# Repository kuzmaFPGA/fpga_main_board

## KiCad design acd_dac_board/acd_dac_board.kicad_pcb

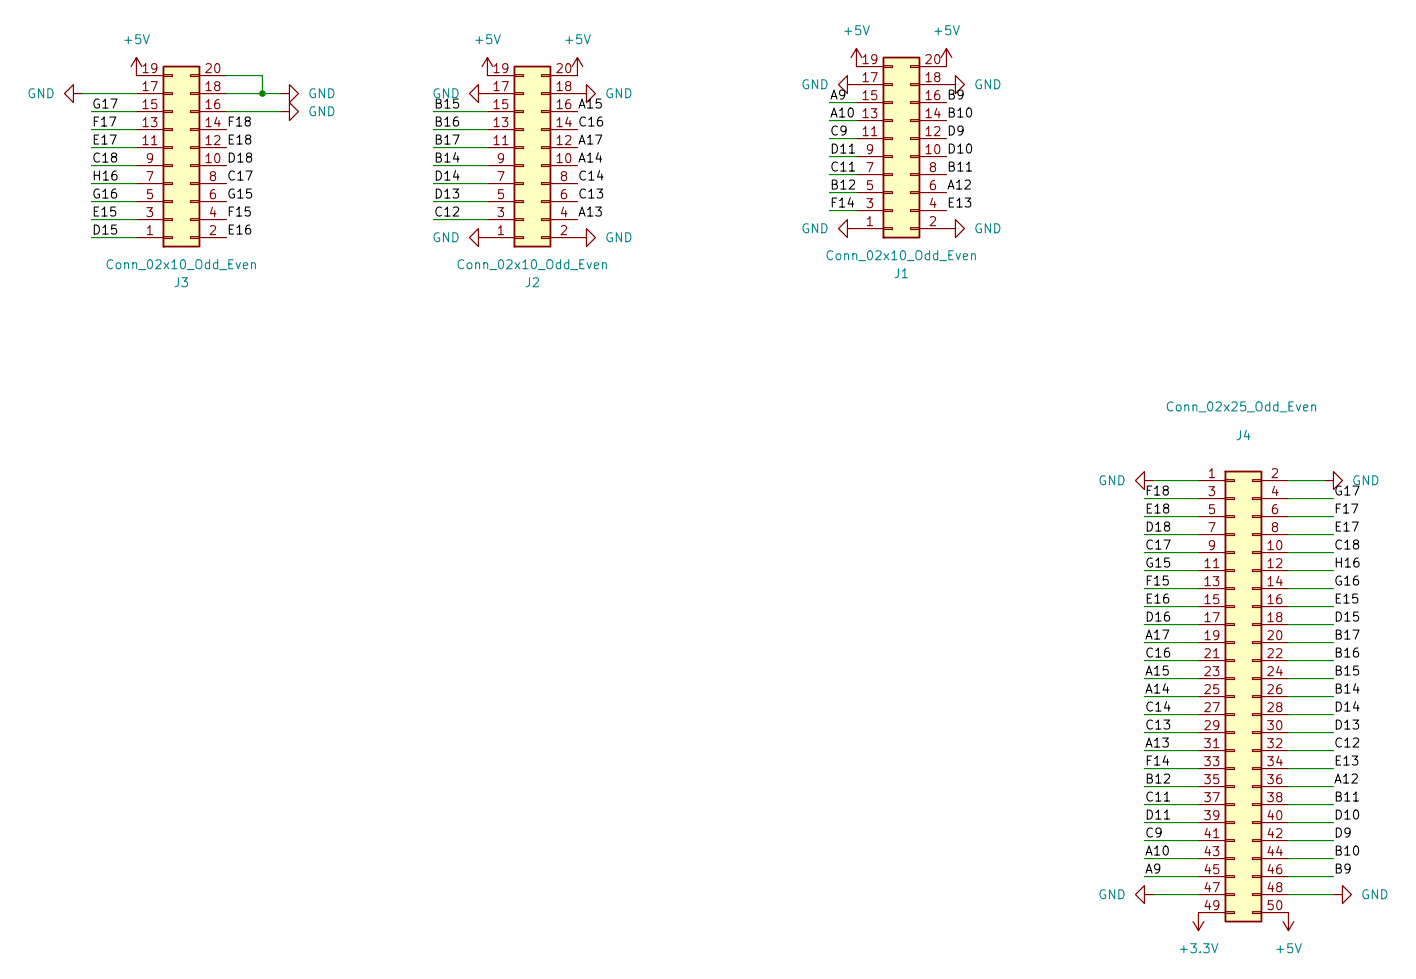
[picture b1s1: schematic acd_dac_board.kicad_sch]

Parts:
J1, J2, J3: Conn_02x10_Odd_Even; PinSocket_2x10_P2.54mm_Vertical
J4: Conn_02x25_Odd_Even; PinHeader_2x25_P2.54mm_Horizontal

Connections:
+3.3V: J4.49
+5V: J1.19, J1.20, J2.19, J2.20, J3.19, J4.50
/A9: J1.15, J4.45
/A10: J1.13, J4.43
/A12: J1.6, J4.36
/A13: J2.4, J4.31
/A14: J2.10, J4.25
/A15: J2.16, J4.23
/A17: J2.12, J4.19
/B9: J1.16, J4.46
/B10: J1.14, J4.44
/B11: J1.8, J4.38
/B12: J1.5, J4.35
/B14: J2.9, J4.26
/B15: J2.15, J4.24
/B16: J2.13, J4.22
/B17: J2.11, J4.20
/C9: J1.11, J4.41
/C11: J1.7, J4.37
/C12: J2.3, J4.32
/C13: J2.6, J4.29
/C14: J2.8, J4.27
/C16: J2.14, J4.21
/C17: J3.8, J4.9
/C18: J3.9, J4.10
/D9: J1.12, J4.42
/D10: J1.10, J4.40
/D11: J1.9, J4.39
/D13: J2.5, J4.30
/D14: J2.7, J4.28
/D15: J3.1, J4.18
/D16: J4.17
/D18: J3.10, J4.7
/E13: J1.4, J4.34
/E15: J3.3, J4.16
/E16: J3.2, J4.15
/E17: J3.11, J4.8
/E18: J3.12, J4.5
/F14: J1.3, J4.33
/F15: J3.4, J4.13
/F17: J3.13, J4.6
/F18: J3.14, J4.3
/G15: J3.6, J4.11
/G16: J3.5, J4.14
/G17: J3.15, J4.4
/H16: J3.7, J4.12
GND: J1.1, J1.2, J1.17, J1.18, J2.1, J2.2, J2.17, J2.18, J3.16, J3.17, J3.18, J3.20, J4.1, J4.2, J4.47, J4.48

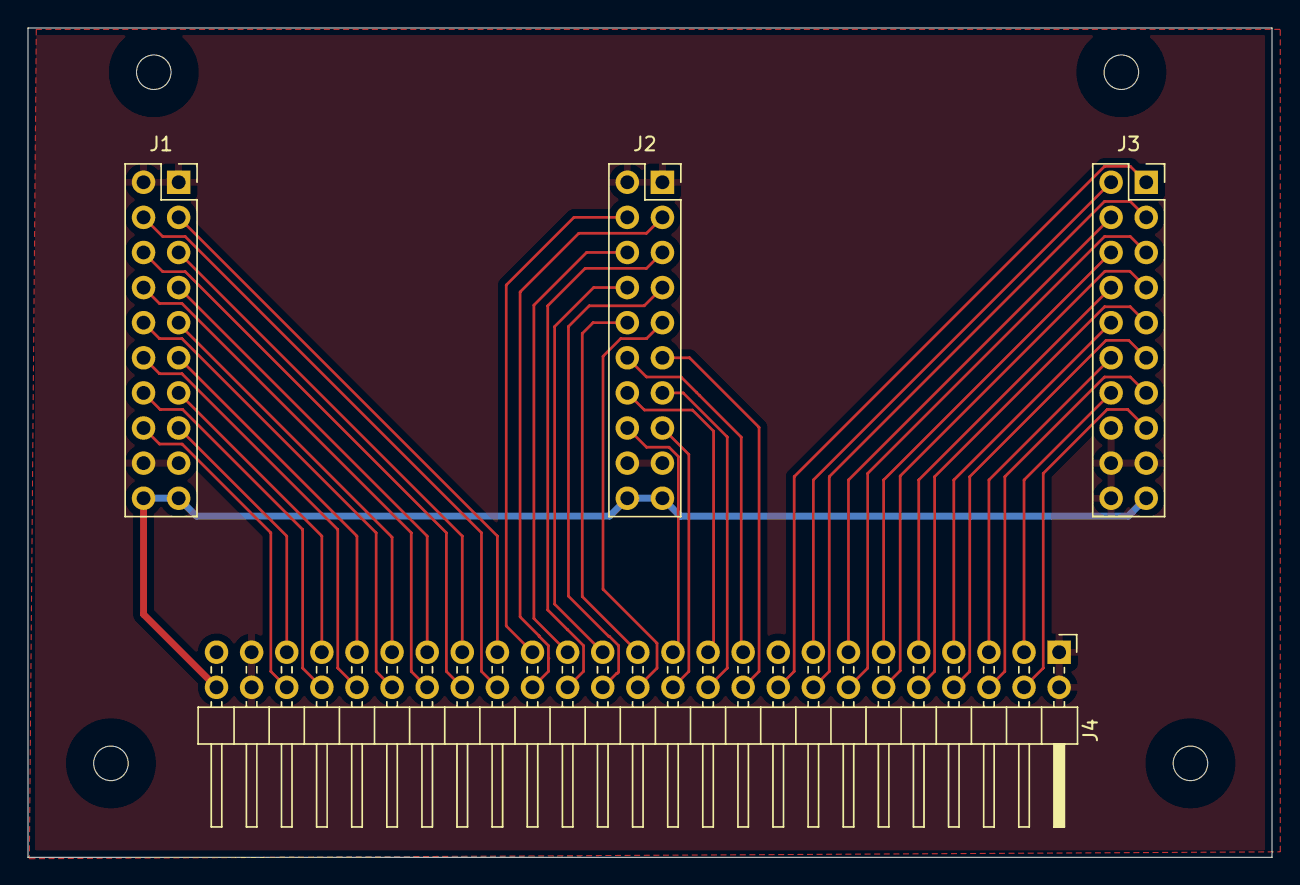
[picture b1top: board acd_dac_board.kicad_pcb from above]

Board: 2 copper layers, 90.0 x 60.0 mm, 4 parts (0 on the bottom side), 45 nets.

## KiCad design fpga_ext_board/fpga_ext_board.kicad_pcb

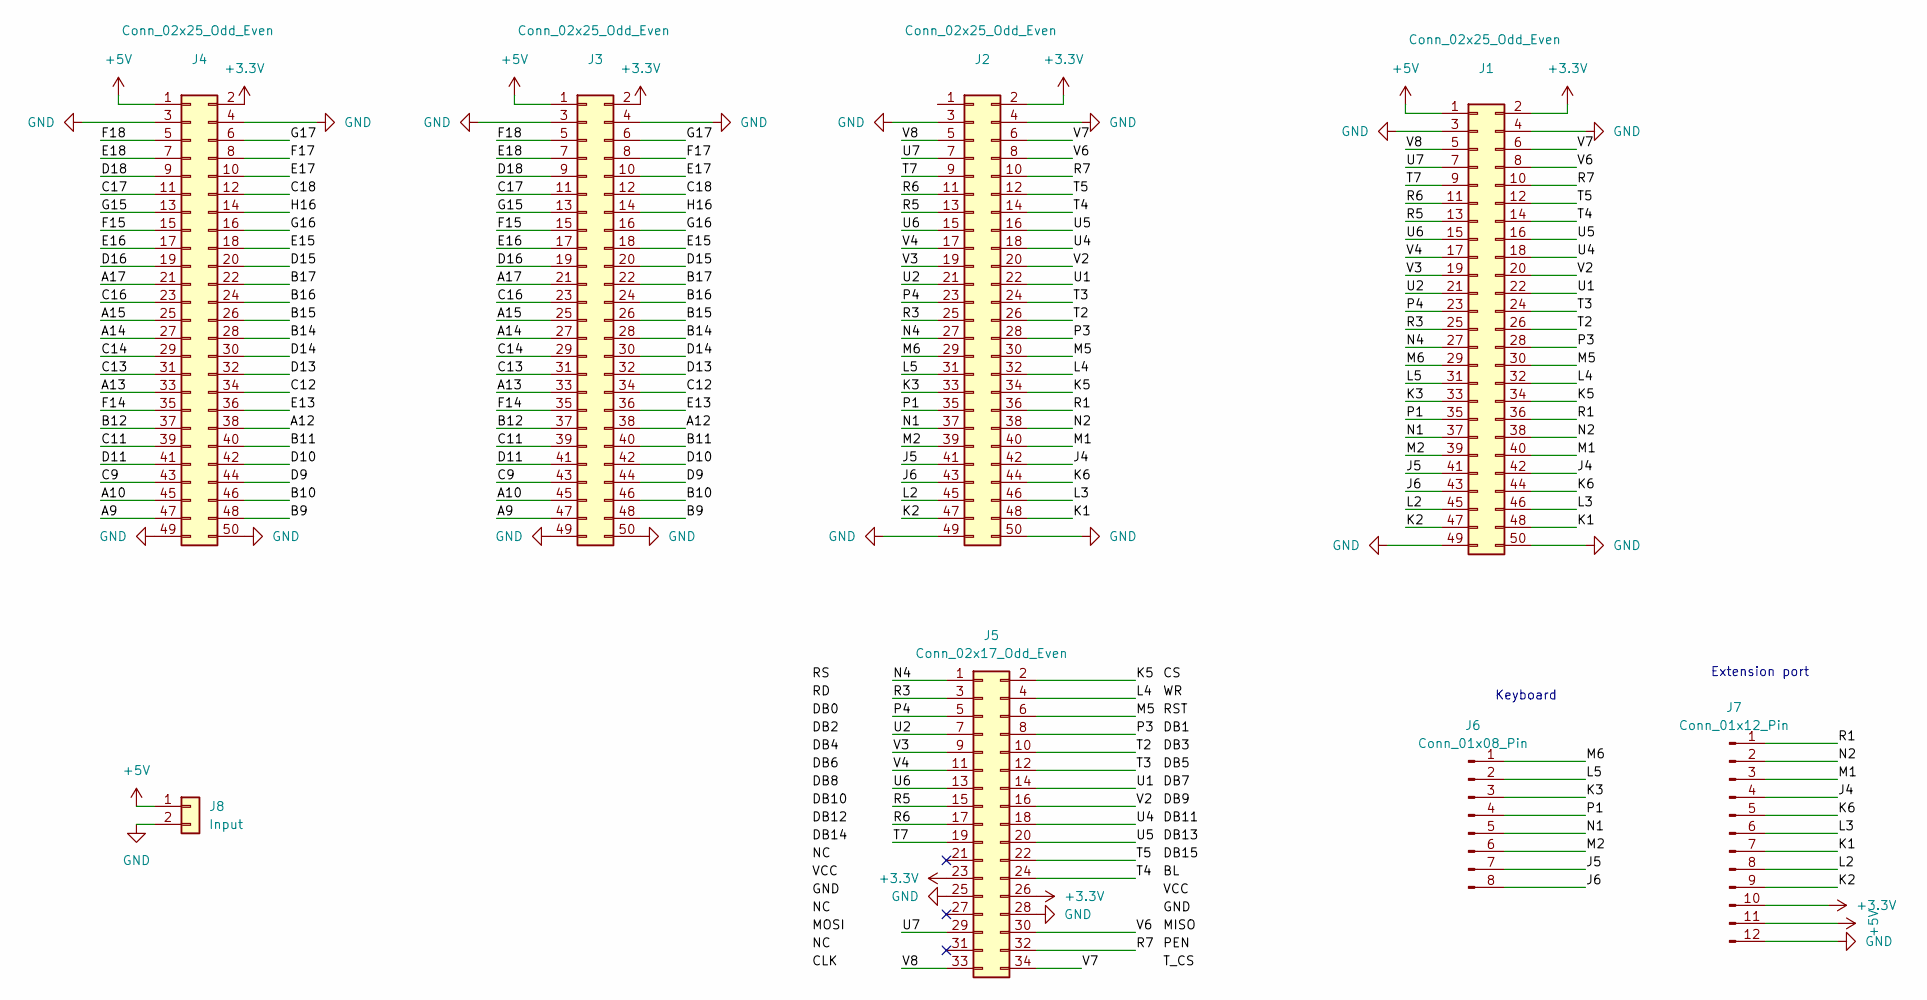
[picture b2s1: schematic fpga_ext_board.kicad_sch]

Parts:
J1, J2, J3, J4: Conn_02x25_Odd_Even; PinSocket_2x25_P2.54mm_Vertical
J5: Conn_02x17_Odd_Even; PinHeader_2x17_P2.54mm_Vertical
J6: Conn_01x08_Pin; PinHeader_1x08_P2.54mm_Vertical
J7: Conn_01x12_Pin; PinHeader_1x12_P2.54mm_Vertical
J8: Input; Molex_Micro-Fit_3.0_43650-0215_1x02_P3.00mm_Vertical

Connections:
+3.3V: J1.2, J2.2, J3.2, J4.2, J5.23, J5.26, J7.10
+5V: J1.1, J3.1, J4.1, J7.11, J8.1
/A9: J3.47, J4.47
/A10: J3.45, J4.45
/A12: J3.38, J4.38
/A13: J3.33, J4.33
/A14: J3.27, J4.27
/A15: J3.25, J4.25
/A17: J3.21, J4.21
/B9: J3.48, J4.48
/B10: J3.46, J4.46
/B11: J3.40, J4.40
/B12: J3.37, J4.37
/B14: J3.28, J4.28
/B15: J3.26, J4.26
/B16: J3.24, J4.24
/B17: J3.22, J4.22
/C9: J3.43, J4.43
/C11: J3.39, J4.39
/C12: J3.34, J4.34
/C13: J3.31, J4.31
/C14: J3.29, J4.29
/C16: J3.23, J4.23
/C17: J3.11, J4.11
/C18: J3.12, J4.12
/D9: J3.44, J4.44
/D10: J3.42, J4.42
/D11: J3.41, J4.41
/D13: J3.32, J4.32
/D14: J3.30, J4.30
/D15: J3.20, J4.20
/D16: J3.19, J4.19
/D18: J3.9, J4.9
/E13: J3.36, J4.36
/E15: J3.18, J4.18
/E16: J3.17, J4.17
/E17: J3.10, J4.10
/E18: J3.7, J4.7
/F14: J3.35, J4.35
/F15: J3.15, J4.15
/F17: J3.8, J4.8
/F18: J3.5, J4.5
/G15: J3.13, J4.13
/G16: J3.16, J4.16
/G17: J3.6, J4.6
/H16: J3.14, J4.14
/J4: J1.42, J2.42, J7.4
/J5: J1.41, J2.41, J6.7
/J6: J1.43, J2.43, J6.8
/K1: J1.48, J2.48, J7.7
/K2: J1.47, J2.47, J7.9
/K3: J1.33, J2.33, J6.3
/K5: J1.34, J2.34, J5.2
/K6: J1.44, J2.44, J7.5
/L2: J1.45, J2.45, J7.8
/L3: J1.46, J2.46, J7.6
/L4: J1.32, J2.32, J5.4
/L5: J1.31, J2.31, J6.2
/M1: J1.40, J2.40, J7.3
/M2: J1.39, J2.39, J6.6
/M5: J1.30, J2.30, J5.6
/M6: J1.29, J2.29, J6.1
/N1: J1.37, J2.37, J6.5
/N2: J1.38, J2.38, J7.2
/N4: J1.27, J2.27, J5.1
/P1: J1.35, J2.35, J6.4
/P3: J1.28, J2.28, J5.8
/P4: J1.23, J2.23, J5.5
/R1: J1.36, J2.36, J7.1
/R3: J1.25, J2.25, J5.3
/R5: J1.13, J2.13, J5.15
/R6: J1.11, J2.11, J5.17
/R7: J1.10, J2.10, J5.32
/T2: J1.26, J2.26, J5.10
/T3: J1.24, J2.24, J5.12
/T4: J1.14, J2.14, J5.24
/T5: J1.12, J2.12, J5.22
/T7: J1.9, J2.9, J5.19
/U1: J1.22, J2.22, J5.14
/U2: J1.21, J2.21, J5.7
/U4: J1.18, J2.18, J5.18
/U5: J1.16, J2.16, J5.20
/U6: J1.15, J2.15, J5.13
/U7: J1.7, J2.7, J5.29
/V2: J1.20, J2.20, J5.16
/V3: J1.19, J2.19, J5.9
/V4: J1.17, J2.17, J5.11
/V6: J1.8, J2.8, J5.30
/V7: J1.6, J2.6, J5.34
/V8: J1.5, J2.5, J5.33
GND: J1.3, J1.4, J1.49, J1.50, J2.3, J2.4, J2.49, J2.50, J3.3, J3.4, J3.49, J3.50, J4.3, J4.4, J4.49, J4.50, J5.25, J5.28, J7.12, J8.2

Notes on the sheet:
Keyboard
Extension port

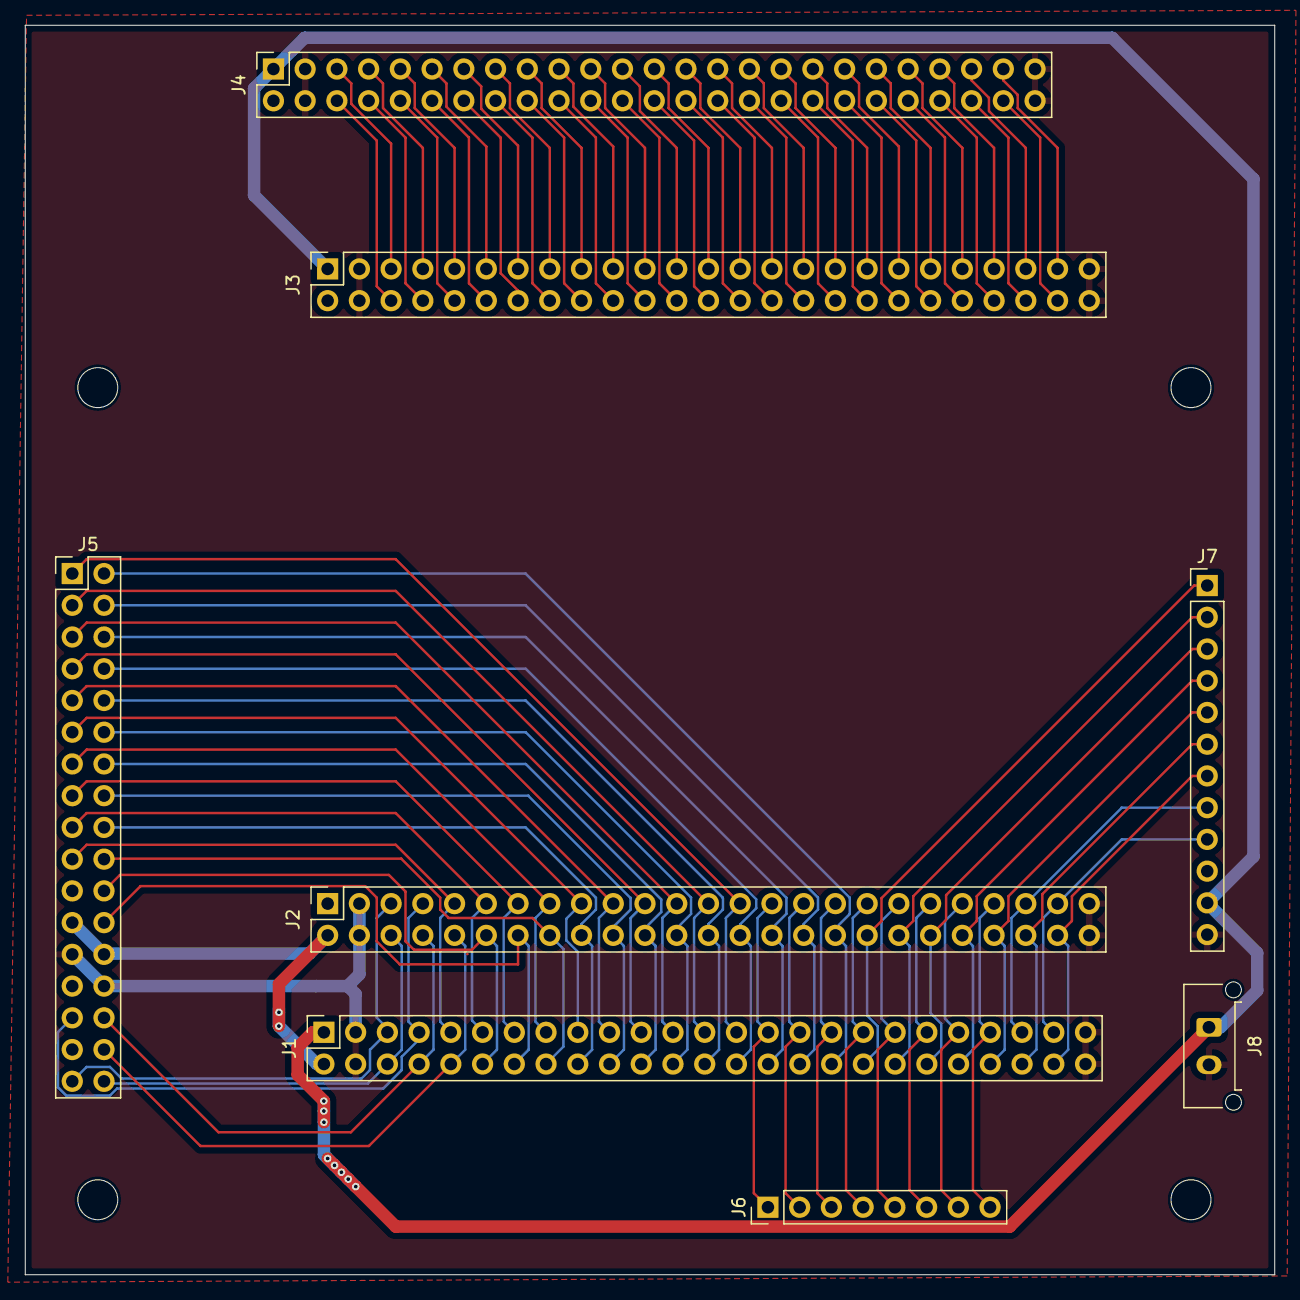
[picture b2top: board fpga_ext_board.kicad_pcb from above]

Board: 2 copper layers, 100.0 x 100.0 mm, 12 parts (0 on the bottom side), 91 nets.

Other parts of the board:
REF1, REF2, REF3, REF4: MountingHole_3.2mm_M3

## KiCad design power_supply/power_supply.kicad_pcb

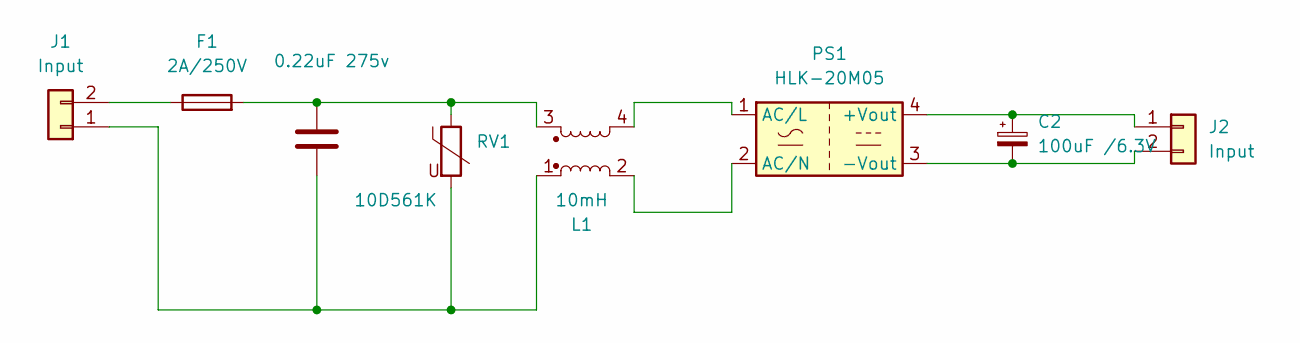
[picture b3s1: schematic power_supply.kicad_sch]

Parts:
C1: 0.22uF 275v; CAPRR2250W80L2650T1050H1650; Part Description 0.1uF 10% 100V Ceramic Capacitor X5R 04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
C2: 100uF /6.3V; CP_Radial_D5.0mm_P2.50mm
F1: 2A/250V; Fuseholder_Cylinder-5x20mm_Stelvio-Kontek_PTF78_Horizontal_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
J1: Input; TE_826576-2_1x02_P3.96mm_Vertical
J2: Input; Molex_Micro-Fit_3.0_43650-0215_1x02_P3.00mm_Vertical
L1: 10mH; IndRing
PS1: HLK-20M05; Converter_ACDC_Hi-Link_HLK-20Mxx
RV1: 10D561K; Bourns_Inc.-MOV-14D471K-MFG

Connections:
unnamed: C1.1, F1.2, L1.3, RV1.1
unnamed: C1.2, J1.1, L1.1, RV1.2
unnamed: F1.1, J1.2
unnamed: C2.1, J2.1, PS1.4 (+Vout)
unnamed: C2.2, J2.2, PS1.3 (-Vout)
unnamed: L1.4, PS1.1 (AC/L)
unnamed: L1.2, PS1.2 (AC/N)

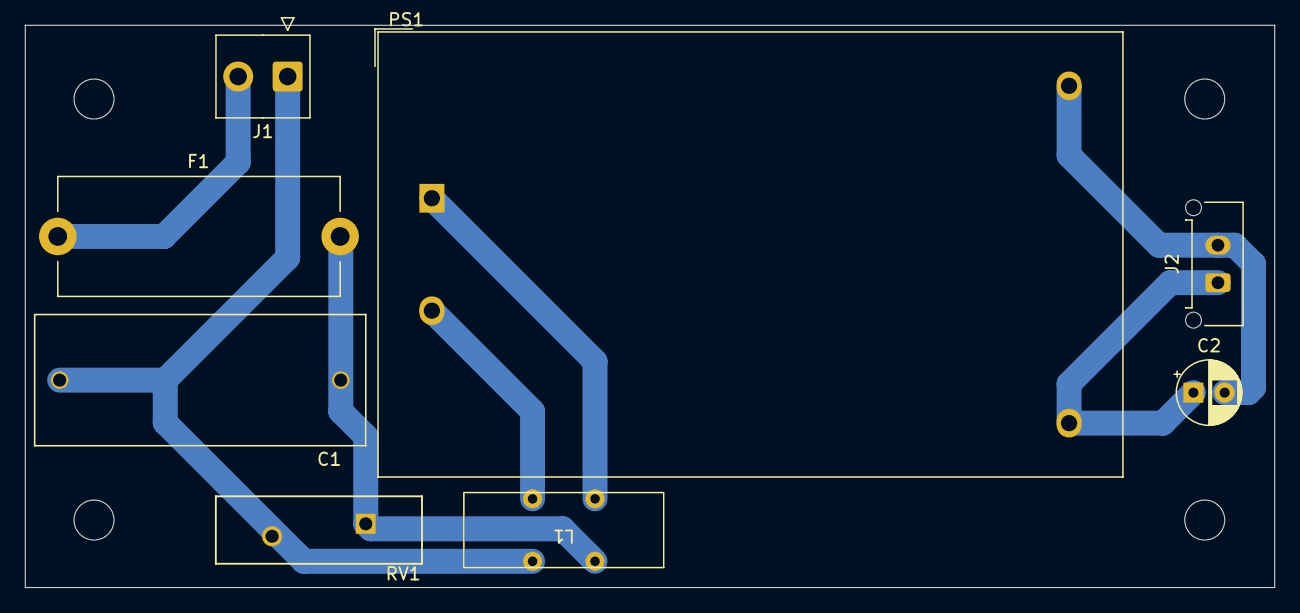
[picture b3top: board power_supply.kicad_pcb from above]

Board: 2 copper layers, 100.0 x 45.0 mm, 12 parts (0 on the bottom side), 7 nets.

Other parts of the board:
hole1, hole1#2, hole1#3, hole1#4: MountingHole_3.2mm_M3

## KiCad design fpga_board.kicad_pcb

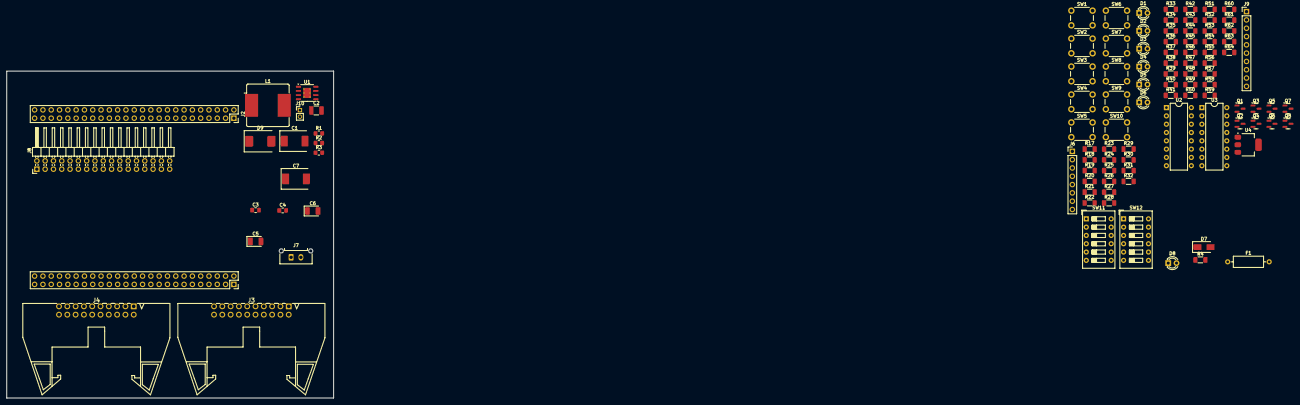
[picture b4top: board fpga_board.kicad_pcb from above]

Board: 2 copper layers, 100.0 x 100.0 mm, 102 parts (0 on the bottom side), 123 nets, no tracks yet.

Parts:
C1, C7: 68uF*35V; CP_EIA-7361-38_AVX-V_Pad2.18x3.30mm_HandSolder
C2: 10uF 50V; C_1210_3225Metric_Pad1.33x2.70mm_HandSolder
C3: 22pF; C_0805_2012Metric_Pad1.18x1.45mm_HandSolder
C4: 22nF; C_0805_2012Metric_Pad1.18x1.45mm_HandSolder
C5, C6: 22uF; CP_EIA-3528-21_Kemet-B_Pad1.50x2.35mm_HandSolder
D1, D2, D3, D4, D5, D6, D8: LED; LED_D3.0mm
D7: STPS2L60; D_SMA
D9: STPS3L40S; D_SMC
F1: Fuse; R_Axial_DIN0309_L9.0mm_D3.2mm_P12.70mm_Horizontal
J2: FPGA_board
J3: 165MDAC; CONN-TH_DS1011-20RBSIB7-B
J4: 65MADC; CONN-TH_DS1011-20RBSIB7-B
J6: Conn_01x08; PinHeader_1x08_P2.54mm_Vertical
J7: Input; Molex_Micro-Fit_3.0_43650-0215_1x02_P3.00mm_Vertical
J8: Conn_02x17_Odd_Even; PinHeader_2x17_P2.54mm_Horizontal
J9: Conn_01x10_Pin; PinHeader_1x10_P2.54mm_Vertical
J10: Conn_01x02; PinHeader_1x02_P2.00mm_Vertical
L1: 27uH; L_Bourns_SRR1208_12.7x12.7mm
Q1, Q2, Q3, Q4, Q5, Q6, Q7, Q8: 2N7002H; SOT-23
R1: 6.2k; R_0805_2012Metric_Pad1.20x1.40mm_HandSolder
R2: 13k; R_0805_2012Metric_Pad1.20x1.40mm_HandSolder
R3: 4.3k; R_0805_2012Metric_Pad1.20x1.40mm_HandSolder
R4, R17, R18, R19, R20, R21, R22: 330; R_1206_3216Metric_Pad1.30x1.75mm_HandSolder
R23, R24, R25, R26, R27, R28, R29, R30, R31, R32, R41, R42, R47, R50, R53, R56, R59, R62: 10k; R_1206_3216Metric_Pad1.30x1.75mm_HandSolder
R33, R34, R35, R36, R37, R38, R39, R40: 1k; R_1206_3216Metric_Pad1.30x1.75mm_HandSolder
R43, R45, R48, R51, R54, R57, R60, R63: 100k; R_1206_3216Metric_Pad1.30x1.75mm_HandSolder
R44, R46, R49, R52, R55, R58, R61, R64: 220; R_1206_3216Metric_Pad1.30x1.75mm_HandSolder
SW1, SW2, SW3, SW4, SW5, SW6, SW7, SW8, SW9, SW10: SW_Push; SW_PUSH_6mm
SW11, SW12: SW_DIP_x06; SW_DIP_SPSTx06_Slide_9.78x17.42mm_W7.62mm_P2.54mm
U1: L5973D013TR; HSOP-8-1EP_3.9x4.9mm_P1.27mm_EP2.41x3.1mm_ThermalVias
U2, U3: LTV-847; DIP-16_W7.62mm
U4: AMS1117-3.3; SOT-223-3_TabPin2

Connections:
+3.3V: J2.2, J2.52 (Pin_2), J6.1, R23.2, R24.2, R25.2, R26.2, R27.2, R28.2, R29.2, R30.2, R31.2, R32.2, R33.1, R34.1, R35.1, R36.1, R37.1, R38.1, R39.1, R40.1
+5V: C5.1, C6.1, J2.1, J3.2, J4.1, J4.2, L1.2, R2.2
+VDC: U2.1, U2.3, U2.5, U2.7, U3.1, U3.3, U3.5, U3.7, U4.2 (VO)
/A13: J2.83 (Pin_33), J4.6
/A14: J2.77 (Pin_27), J4.12
/A15: J2.75 (Pin_25), J4.14
/A17: J2.71 (Pin_21), J4.18
/B14: J2.78 (Pin_28), J4.11
/B15: J2.76 (Pin_26), J4.13
/B16: J2.74 (Pin_24), J4.15
/B17: J2.72 (Pin_22), J4.17
/C12: J2.84 (Pin_34), J4.5
/C13: J2.81 (Pin_31), J4.8
/C14: J2.79 (Pin_29), J4.10
/C16: J2.73 (Pin_23), J4.16
/C17: J2.61 (Pin_11), J3.14
/C18: J2.62 (Pin_12), J3.13
/D13: J2.82 (Pin_32), J4.7
/D14: J2.80 (Pin_30), J4.9
/D15: J2.70 (Pin_20), J3.5
/D16: J2.69 (Pin_19), J6.2, SW11.12, SW12.1
/D18: J2.59 (Pin_9), J3.16
/E15: J2.68 (Pin_18), J3.7
/E16: J2.67 (Pin_17), J3.8
/E17: J2.60 (Pin_10), J3.15
/E18: J2.57 (Pin_7), J3.18
/F15: J2.65 (Pin_15), J3.10
/F17: J2.58 (Pin_8), J3.17
/F18: J2.55 (Pin_5), J3.20
/G15: J2.63 (Pin_13), J3.12
/G16: J2.66 (Pin_16), J3.9
/G17: J2.56 (Pin_6), J3.19
/H16: J2.64 (Pin_14), J3.11
/J4: J2.42, SW1.2
/J5: J2.41, J6.3, SW11.11, SW12.2
/J6: J2.43, J6.5, SW11.9, SW12.4
/K1: J2.48, SW4.2
/K2: J2.47, J6.7, SW11.7, SW12.6
/K6: J2.44, SW2.2
/L2: J2.45, J6.6, SW11.8, SW12.5
/L3: J2.46, SW3.2
/LCD/VCC: J8.9, J8.12
/M2: J2.39, J6.4, SW11.10, SW12.3
/M5: J2.30, R36.2, U2.10
/R5: J2.13, R33.2, U2.16
/R6: J2.11, R39.2, U3.12
/T4: J2.14, R38.2, U3.14
/T7: J2.9, R40.2, U3.10
/U4: J2.18, R34.2, U2.14
/U5: J2.16, R37.2, U3.16
/U6: J2.15, R35.2, U2.12
GND: C1.2, C2.2, C3.2, C5.2, C6.2, C7.2, D9.2 (A), J2.3, J2.4, J2.49, J2.50, J2.53 (Pin_3), J2.54 (Pin_4), J2.99 (Pin_49), J2.100 (Pin_50), J3.1, J3.3, J3.4, J3.6, J4.3, J4.4, J4.19, J4.20, J6.8, J7.1, J8.7, J8.10, J10.2, R1.1, R3.1, R17.1, R18.1, R19.1, R20.1, R21.1, R22.1, U1.7 (GND), U1.9 (EP), U2.9, U2.11, U2.13, U2.15, U3.9, U3.11, U3.13, U3.15
GND2: J9.10, Q1.2 (S), Q2.2 (S), Q3.2 (S), Q4.2 (S), Q5.2 (S), Q6.2 (S), Q7.2 (S), Q8.2 (S), R43.2, R45.2, R48.2, R51.2, R54.2, R57.2, R60.2, R63.2, U4.1 (GND)
unnamed: C4.2, R1.2
unnamed: D1.2 (A), SW11.1
unnamed: D1.1 (K), R17.2
unnamed: D2.2 (A), SW11.2
unnamed: D2.1 (K), R18.2
unnamed: D3.2 (A), SW11.3
unnamed: D3.1 (K), R19.2
unnamed: D4.2 (A), SW11.4
unnamed: D4.1 (K), R20.2
unnamed: D5.2 (A), SW11.5
unnamed: D5.1 (K), R21.2
unnamed: D6.2 (A), SW11.6
unnamed: D6.1 (K), R22.2
unnamed: D7.2 (A), F1.2
unnamed: D8.1 (K), R4.2
unnamed: D9.1 (K), L1.1, U1.1 (OUT)
unnamed: F1.1, J7.2
unnamed: J9.2, R59.2
unnamed: J9.3, R42.2
unnamed: J9.4, R41.2
unnamed: J9.5, R47.2
unnamed: J9.6, R50.2
unnamed: J9.7, R53.2
unnamed: J9.8, R56.2
unnamed: J9.9, R62.2
unnamed: J10.1, U1.3 (INH)
unnamed: Q1.3 (D), R44.1
unnamed: Q1.1 (G), R42.1, R43.1
unnamed: Q2.3 (D), R46.1
unnamed: Q2.1 (G), R41.1, R45.1
unnamed: Q3.3 (D), R49.1
unnamed: Q3.1 (G), R47.1, R48.1
unnamed: Q4.3 (D), R52.1
unnamed: Q4.1 (G), R50.1, R51.1
unnamed: Q5.3 (D), R55.1
unnamed: Q5.1 (G), R53.1, R54.1
unnamed: Q6.3 (D), R58.1
unnamed: Q6.1 (G), R56.1, R57.1
unnamed: Q7.3 (D), R61.1
unnamed: Q7.1 (G), R59.1, R60.1
unnamed: Q8.3 (D), R64.1
unnamed: Q8.1 (G), R62.1, R63.1
unnamed: R23.1, SW5.2
unnamed: R24.1, SW6.2
unnamed: R25.1, SW7.2
unnamed: R26.1, SW8.2
unnamed: R27.1, SW9.2
unnamed: R28.1, SW10.2
unnamed: R29.1, SW1.1
unnamed: R30.1, SW2.1
unnamed: R31.1, SW3.1
unnamed: R32.1, SW4.1
unnamed: R44.2, U3.4
unnamed: R46.2, U3.6
unnamed: R49.2, U3.8
unnamed: R52.2, U2.2
unnamed: R55.2, U2.4
unnamed: R58.2, U2.6
unnamed: R61.2, U3.2
unnamed: R64.2, U2.8
unnamed: SW10.1, SW12.7
unnamed: SW9.1, SW12.8
unnamed: SW8.1, SW12.9
unnamed: SW7.1, SW12.10
unnamed: SW6.1, SW12.11
unnamed: SW5.1, SW12.12
unnamed: C3.1, C4.1, U1.4 (COMP)
unnamed: R2.1, R3.2, U1.5 (FB)
POWER_IN: C1.1, C2.1, C7.1, D7.1 (K), U1.8 (VCC)
VDD: J9.1, U4.3 (VI)

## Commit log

2025-02-02 Fix errors with LCD connection
2025-02-06 add new type of LCD. start rework pcb
2025-02-06 edit lcd symbol
2025-02-07 change logick
    на платі будуть роз'єми, цап ацп підключаються плоским кабелем
2025-02-08 Make 3d model for ADC and FPGA. Trying to assembly
2025-02-09 Додав модель ЦАП. тримача під плати АЦП ЦАП (не завершено)
2025-02-12 update adc_dac board
2025-02-15 add files
2025-02-16 add initial version of holder
2025-02-19 route adc_dac board (fix errors). Finish first version of holder
2025-02-21 add power supplay project
2025-02-22 update powersupply pcb
2025-03-23 add front panel
2025-03-23 continue work
2025-03-23 continue work. add files
2025-03-30 update base board holes
2025-04-24 fix adc board pinout
